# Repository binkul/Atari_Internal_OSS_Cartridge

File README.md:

# PCB for internal OSS cartridge

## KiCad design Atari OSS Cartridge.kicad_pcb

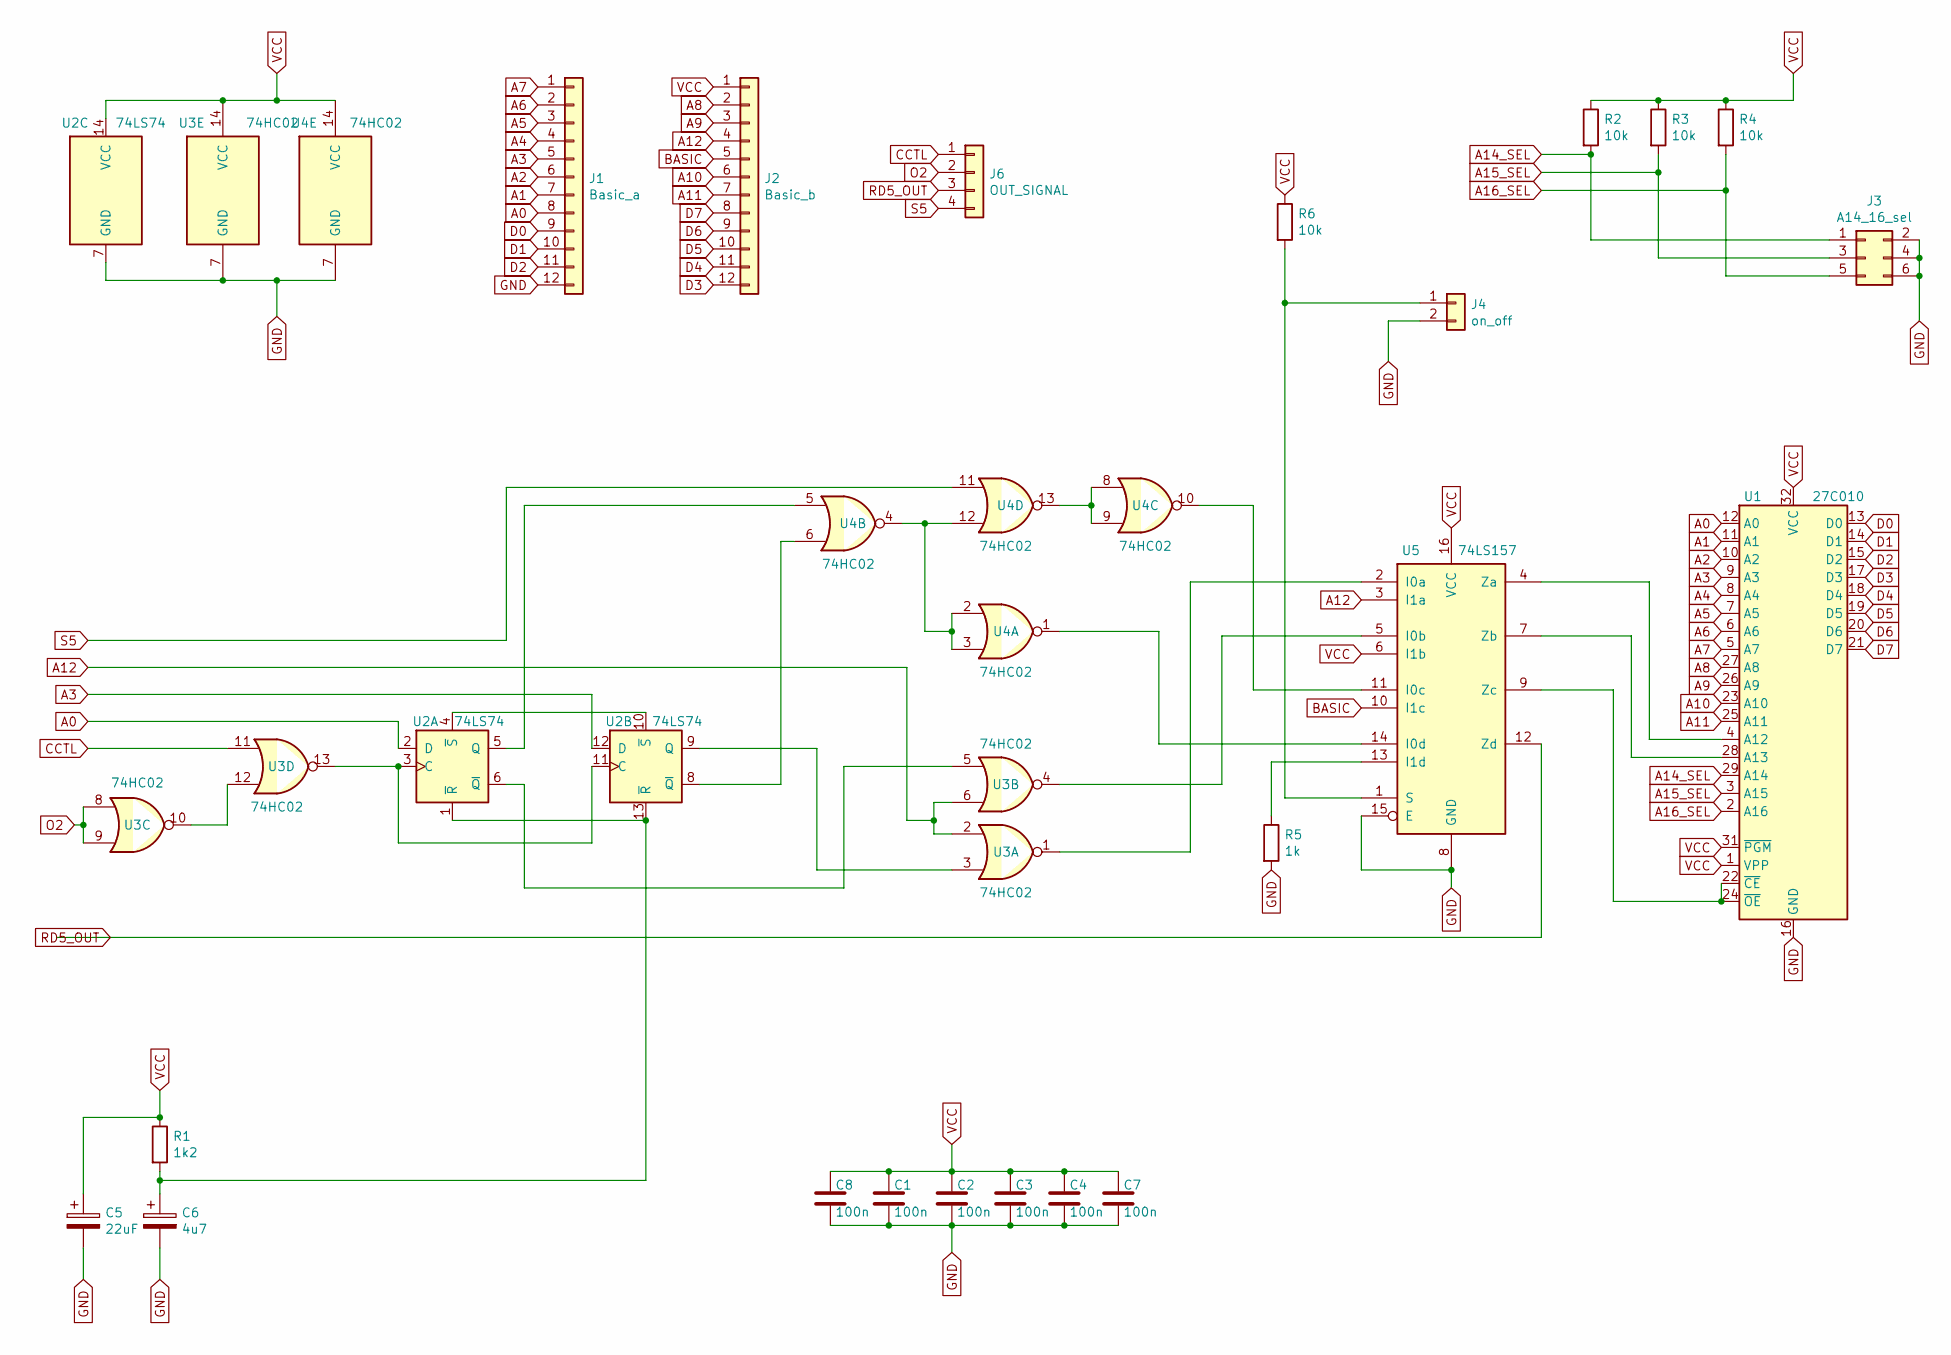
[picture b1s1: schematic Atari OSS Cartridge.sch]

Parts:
C1, C2, C3, C4, C7, C8: 100n; C_0603_1608Metric_Pad1.05x0.95mm_HandSolder
C5: 22uF; CP_EIA-3528-21_Kemet-B_Pad1.50x2.35mm_HandSolder
C6: 4u7; CP_EIA-3528-21_Kemet-B_Pad1.50x2.35mm_HandSolder
J1: Basic_a; PinHeader_1x12_P2.54mm_Vertical_thin
J2: Basic_b; PinHeader_1x12_P2.54mm_Vertical_thin
J3: A14_16_sel; PinHeader_2x03_P2.54mm_Vertical
J4: on_off; PinHeader_1x02_P2.54mm_Vertical
J6: OUT_SIGNAL; PinHeader_1x04_P2.54mm_Vertical
R1: 1k2; R_1206_3216Metric_Pad1.42x1.75mm_HandSolder
R2, R3, R4, R6: 10k; R_0603_1608Metric_Pad1.05x0.95mm_HandSolder
R5: 1k; R_0603_1608Metric_Pad1.05x0.95mm_HandSolder
U1: 27C010; PLCC-32_THT-Socket
U2: 74LS74; SOIC-14_3.9x8.7mm_P1.27mm
U3, U4: 74HC02; SOIC-14_3.9x8.7mm_P1.27mm
U5: 74LS157; SOIC-16_3.9x9.9mm_P1.27mm

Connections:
A0: J1.8, U1.12 (A0), U2.2 (D)
A1: J1.7, U1.11 (A1)
A2: J1.6, U1.10 (A2)
A3: J1.5, U1.9 (A3), U2.12 (D)
A4: J1.4, U1.8 (A4)
A5: J1.3, U1.7 (A5)
A6: J1.2, U1.6 (A6)
A7: J1.1, U1.5 (A7)
A8: J2.2, U1.27 (A8)
A9: J2.3, U1.26 (A9)
A10: J2.6, U1.23 (A10)
A11: J2.7, U1.25 (A11)
A12: J2.4, U3.2, U3.6, U5.3 (I1a)
A14_SEL: J3.1, R2.2, U1.29 (A14)
A15_SEL: J3.3, R3.2, U1.3 (A15)
A16_SEL: J3.5, R4.2, U1.2 (A16)
BASIC: J2.5, U5.10 (I1c)
CCTL: J6.1, U3.11
D0: J1.9, U1.13 (D0)
D1: J1.10, U1.14 (D1)
D2: J1.11, U1.15 (D2)
D3: J2.12, U1.17 (D3)
D4: J2.11, U1.18 (D4)
D5: J2.10, U1.19 (D5)
D6: J2.9, U1.20 (D6)
D7: J2.8, U1.21 (D7)
GND: C1.2, C2.2, C3.2, C4.2, C5.2, C6.2, C7.2, C8.2, J1.12, J3.2, J3.4, J3.6, J4.2, R5.2, U1.16 (GND), U2.7 (GND), U3.7 (GND), U4.7 (GND), U5.8 (GND), U5.15 (E)
unnamed: C6.1, R1.2, U2.1 (~R), U2.13 (~R)
unnamed: J4.1, R6.2, U5.1 (S)
unnamed: R5.1, U5.13 (I1d)
unnamed: U1.4 (A12), U5.4 (Za)
unnamed: U1.22 (~CE), U1.24 (~OE), U5.9 (Zc)
unnamed: U1.28 (A13), U5.7 (Zb)
unnamed: U2.5 (Q), U4.5
unnamed: U2.6 (~Q), U3.5
unnamed: U2.8 (~Q), U4.6
unnamed: U2.9 (Q), U3.3
unnamed: U2.4 (~S), U2.10 (~S)
unnamed: U2.3 (C), U2.11 (C), U3.13
unnamed: U3.1, U5.2 (I0a)
unnamed: U3.4, U5.5 (I0b)
unnamed: U3.10, U3.12
unnamed: U4.1, U5.14 (I0d)
unnamed: U4.10, U5.11 (I0c)
unnamed: U4.2, U4.3, U4.4, U4.12
unnamed: U4.8, U4.9, U4.13
O2: J6.2, U3.8, U3.9
RD5_OUT: J6.3, U5.12 (Zd)
S5: J6.4, U4.11
VCC: C1.1, C2.1, C3.1, C4.1, C5.1, C7.1, C8.1, J2.1, R1.1, R2.1, R3.1, R4.1, R6.1, U1.1 (VPP), U1.31 (~PGM), U1.32 (VCC), U2.14 (VCC), U3.14 (VCC), U4.14 (VCC), U5.6 (I1b), U5.16 (VCC)

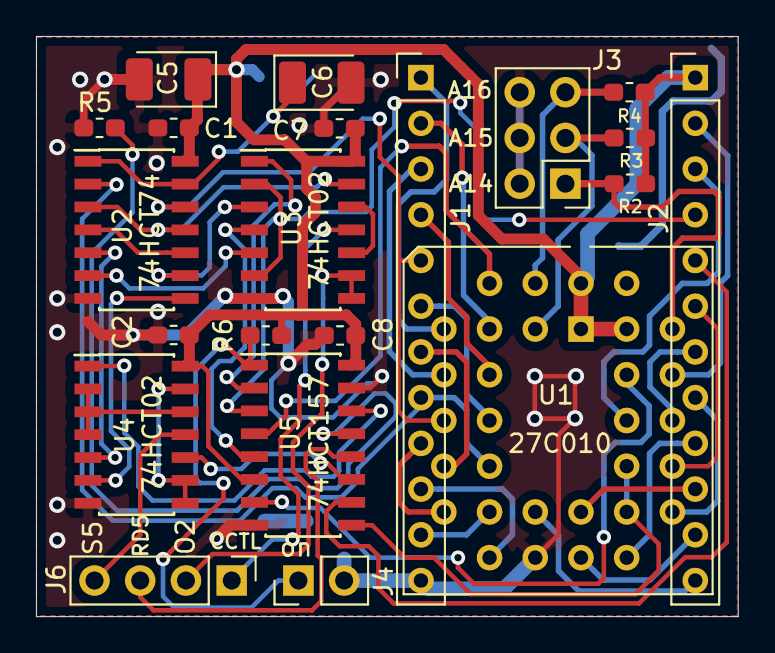
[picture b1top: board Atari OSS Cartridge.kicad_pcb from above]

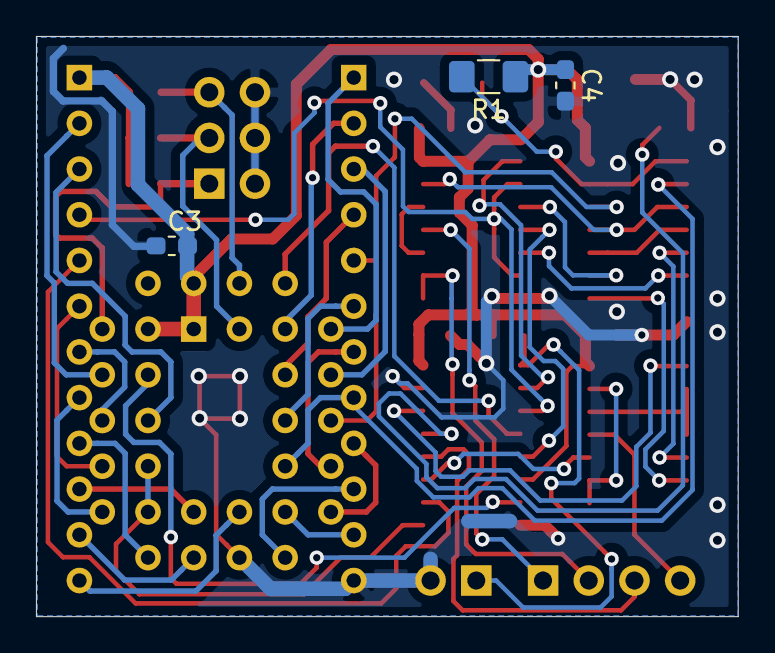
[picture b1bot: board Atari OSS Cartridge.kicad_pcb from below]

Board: 2 copper layers, 39.0 x 32.2 mm, 24 parts (3 on the bottom side), 50 nets.

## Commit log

2021-03-01 Create schematic
2021-03-02 Tracking
2021-03-05 Gerber files
2021-03-07 Improving
